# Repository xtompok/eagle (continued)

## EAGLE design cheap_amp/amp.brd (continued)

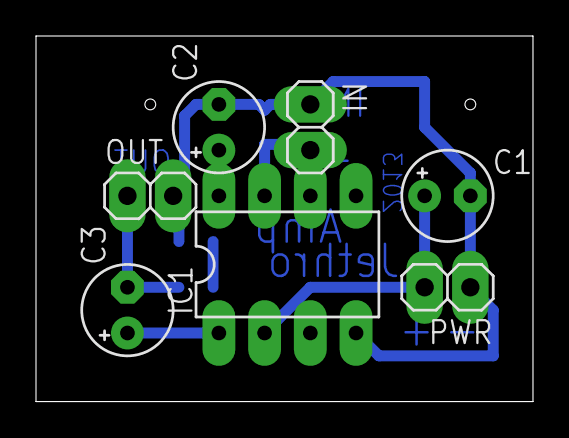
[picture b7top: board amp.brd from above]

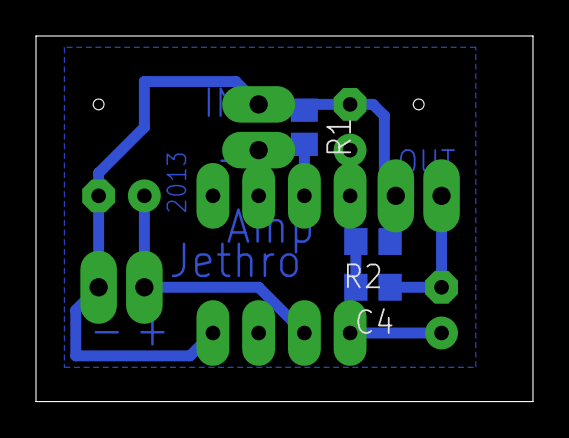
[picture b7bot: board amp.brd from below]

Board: 2 copper layers, 27.6 x 20.3 mm, 10 parts (3 on the bottom side), 7 nets.

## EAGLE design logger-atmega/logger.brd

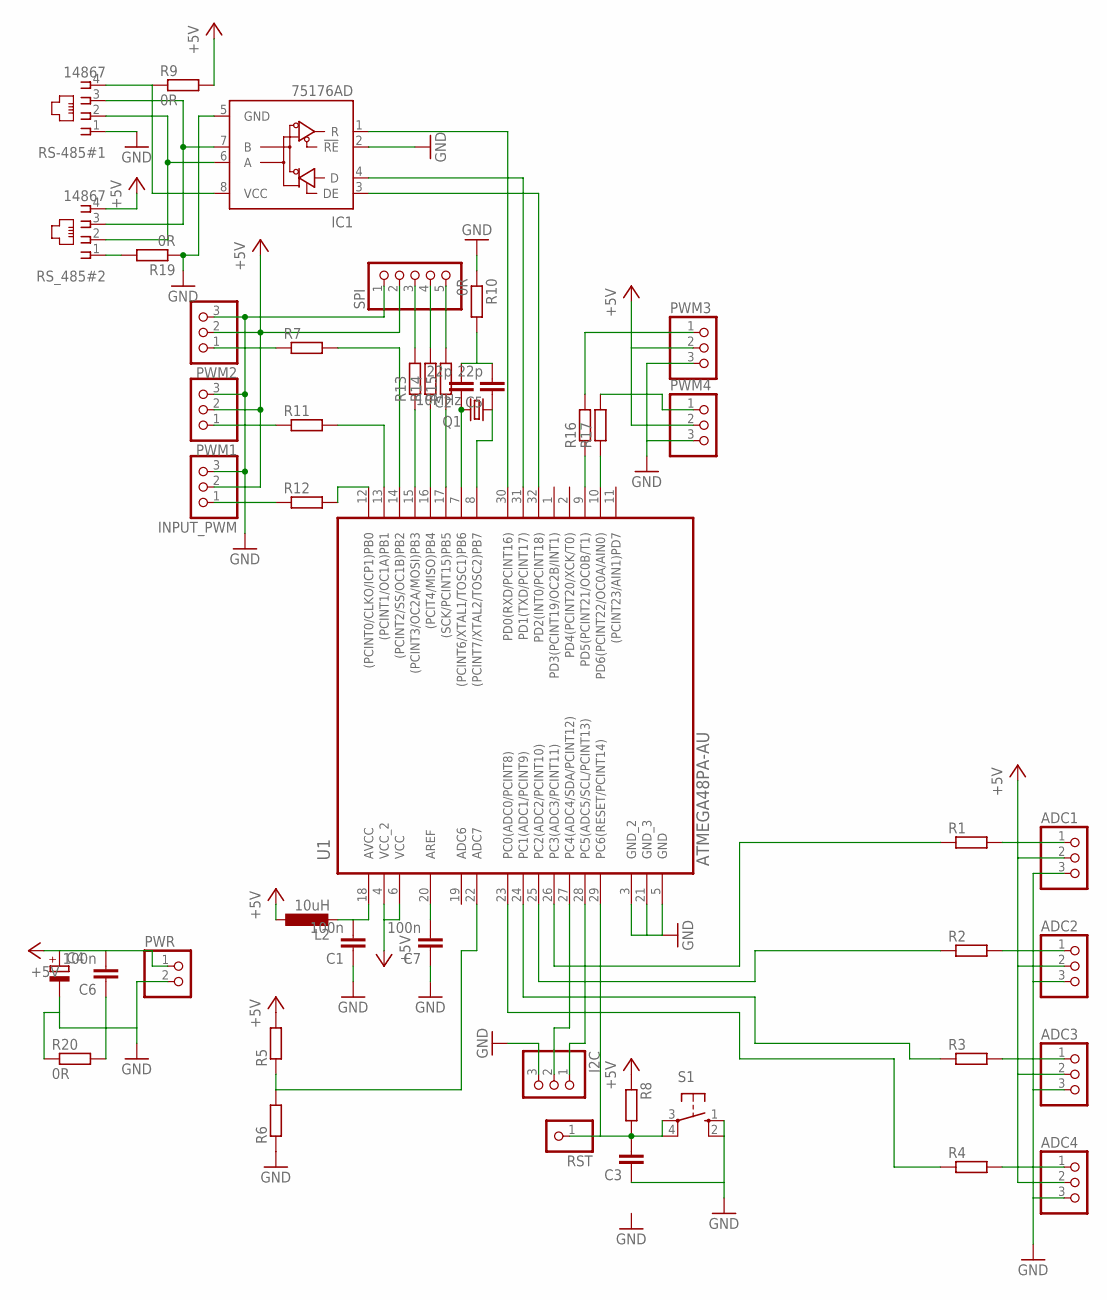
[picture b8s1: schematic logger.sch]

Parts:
ADC1, ADC2, ADC3, ADC4: PINHD-1X3; 1X03
C1, C6, C7: 100n; C0805
C2, C5: 22p; C0805
C3: C-EUC0805; C0805
C4: CPOL-EUE2,5-6E; E2,5-6E
I2C: PINHD-1X3; 1X03
IC1: 75176AD; D_R-PDSO-G8
INPUT_PWM: PINHD-1X3; 1X03
L2: 10uH; L1206
PWM1, PWM2, PWM3, PWM4: PINHD-1X3; 1X03
PWR: PINHD-1X2; 1X02
Q1: 10MHz; HC49U-V
R1, R2, R3, R4, R5, R7, R8, R11, R12, R13, R14, R15, R16, R17: R-EU_R0805; R0805
R6: R-EU_R1206; R1206
R9, R10, R19, R20: 0R; R1206
RS-485#1: 14867
RST: PINHD-1X1; 1X01
RS_485#2: 14867
S1: 10-XX; B3F-10XX
SPI: PINHD-1X5; 1X05
U1: ATMEGA48PA-AU; QFP80P900X900X120-32N

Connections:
+5V: ADC1.2, ADC2.2, ADC3.2, ADC4.2, C4.+, C6.2, INPUT_PWM.2, L2.1, PWM1.2, PWM2.2, PWM3.2, PWM4.2, PWR.1, R5.2, R8.1, R9.2, RS_485#2.4, SPI.2, U1.4 (VCC_2), U1.6 (VCC)
DE: IC1.3 (DE), U1.32 (PD2(INT0/PCINT18))
GND: ADC1.3, ADC2.3, ADC3.3, ADC4.3, C1.1, C3.1, C4.-, C6.1, C7.1, I2C.3, IC1.2 (!RE), IC1.5 (GND), INPUT_PWM.3, PWM1.3, PWM2.3, PWM3.3, PWM4.3, PWR.2, R6.1, R10.1, R19.1, R20.1, R20.2, RS-485#1.1, S1.1 (S), S1.2 (S1), SPI.1, U1.3 (GND_2), U1.5 (GND), U1.21 (GND_3)
unnamed: IC1.6 (A), RS-485#1.2, RS_485#2.2
unnamed: IC1.7 (B), RS-485#1.3, RS_485#2.3
unnamed: R5.1, R6.2, U1.22 (ADC7)
unnamed: R4.1, U1.23 (PC0(ADC0/PCINT8))
unnamed: ADC4.1, R4.2
unnamed: ADC3.1, R3.2
unnamed: ADC2.1, R2.2
unnamed: ADC1.1, R1.2
unnamed: R3.1, U1.24 (PC1(ADC1/PCINT9))
unnamed: R2.1, U1.25 (PC2(ADC2/PCINT10))
unnamed: R1.1, U1.26 (PC3(ADC3/PCINT11))
unnamed: INPUT_PWM.1, R12.1
unnamed: R15.2, SPI.5
unnamed: R14.2, SPI.4
unnamed: C3.2, R8.2, RST.1, S1.3, S1.4 (P1), U1.29 (PC6(RESET/PCINT14))
unnamed: C2.1, Q1.2, U1.7 ((PCINT6/XTAL1/TOSC1)PB6)
unnamed: R13.2, SPI.3
unnamed: C5.1, Q1.1, U1.8 ((PCINT7/XTAL2/TOSC2)PB7)
unnamed: C1.2, L2.2, U1.18 (AVCC)
unnamed: IC1.8 (VCC), R9.1, RS-485#1.4
unnamed: I2C.1, U1.28 (PC5(ADC5/SCL/PCINT13))
unnamed: I2C.2, U1.27 (PC4(ADC4/SDA/PCINT12))
unnamed: PWM1.1, R11.1
unnamed: PWM2.1, R7.1
unnamed: R13.1, U1.15 ((PCINT3/OC2A/MOSI)PB3)
unnamed: R14.1, U1.16 ((PCIT4/MISO)PB4)
unnamed: R16.1, U1.9 (PD5(PCINT21/OC0B/T1))
unnamed: R17.1, U1.10 (PD6(PCINT22/OC0A/AIN0))
unnamed: R15.1, U1.17 ((SCK/PCINT15)PB5)
unnamed: R19.2, RS_485#2.1
unnamed: R12.2, U1.12 ((PCINT0/CLKO/ICP1)PB0)
unnamed: R11.2, U1.13 ((PCINT1/OC1A)PB1)
unnamed: R7.2, U1.14 ((PCINT2/SS/OC1B)PB2)
unnamed: C7.2, U1.20 (AREF)
unnamed: C2.2, C5.2, R10.2
unnamed: PWM4.1, R17.2
unnamed: PWM3.1, R16.2
RX: IC1.1 (R), U1.30 (PD0(RXD/PCINT16))
TX: IC1.4 (D), U1.31 (PD1(TXD/PCINT17))

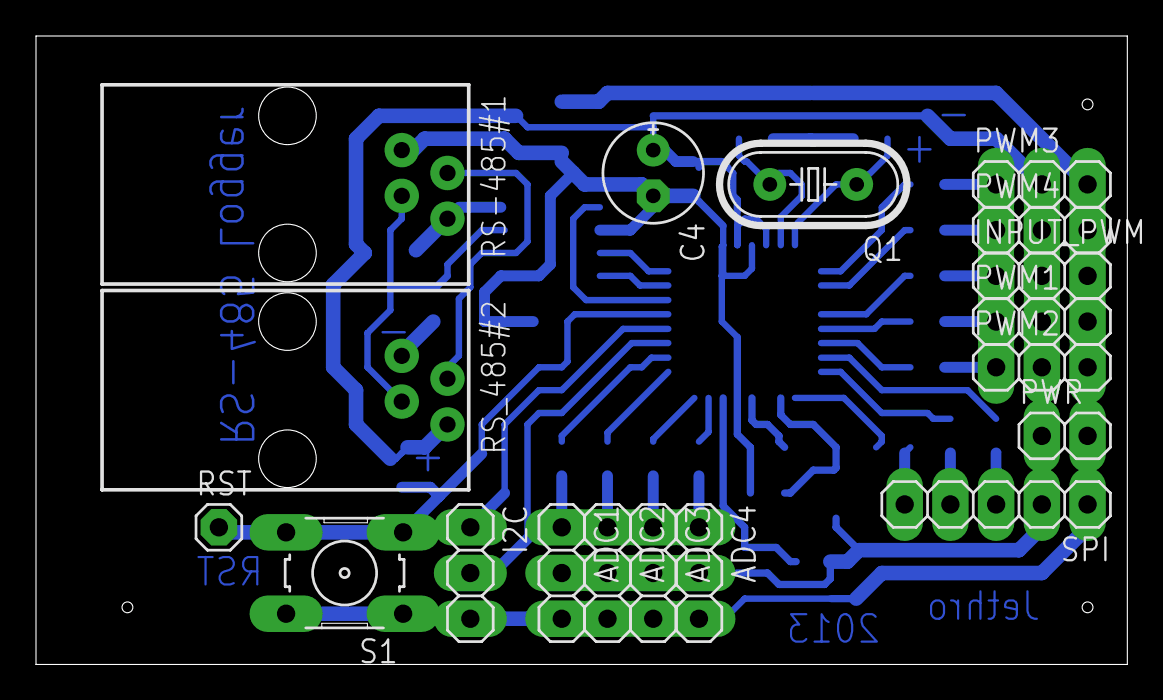
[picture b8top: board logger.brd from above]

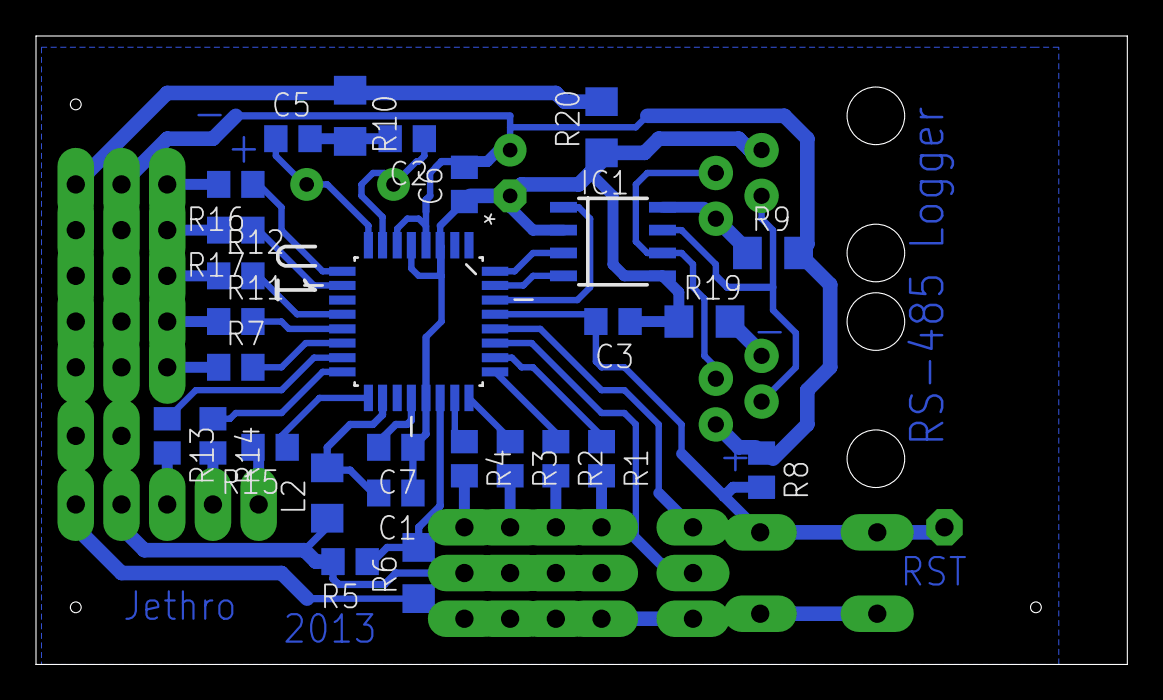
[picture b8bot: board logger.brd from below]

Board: 2 copper layers, 60.6 x 34.9 mm, 46 parts (28 on the bottom side), 42 nets.

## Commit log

2013-03-24 Breakout for magnetic encoder.
2013-03-24 removed unwanted files
2013-03-24 Added .gitignore
2013-03-24 Added description.
2013-03-24 Added logger.
2013-03-24 Added description
2013-03-24 Ignore .DS_Store
2013-03-25 Bugfixes, partially routed.
2013-03-27 Routed.
2013-03-27 Odhad ceny loggeru.
2013-03-27 Final changes.
2013-04-04 Syncing with repository
2013-04-04 copy of logger, wil be magnetic decoder.
2013-04-04 Magnetic encode with MSP430 board
2013-04-05 Commit before merge
2013-04-05 Added new logger, which will have atmega
2013-04-09 Final borad edits and ps for print
2013-04-09 Fix PS
2013-04-10 ATMega logger routed.
2013-04-24 Obrazek pro Cyrila
2013-04-26 Upravy desky i schematu, snad definitivni.
    Odebrana zenerka, budu verit vnitrni referenci
    Pridana civka na analogovou zem
    Pridan napajeci konektor
    Napajeci cesty rozsireny
    Doplneny napisy
    Vylito medi
2013-04-30 Pridan kondenzator na AREF
2013-09-10 Added cheap amplifier with TDA2822M
2013-09-22 Added 2013 to board. added .png file for print.
2013-12-20 Added converter 12V -> 5V with MC34063
2013-12-20 + Napajeci deska na robota
2013-12-20 Doplneny hodnosty soucastek
2013-12-21 Update napajeniMOB.brd
    Takto byla deska vyrobena 20.12.2013
2013-12-21 Update napajeniMOB.sch
    Takto byla deska vyrobena 20.12.2013
2013-12-26 + Added values of parts.
2014-01-04 Changed layout and some parts.
2014-07-26 Added circuit for generator from bicycle.
2014-07-26 Auto-updated eagle.epf
2014-07-26 Use N-channel MOSFET with pulldown.
2014-07-26 First version routed.
2014-07-27 Routed board.
2014-07-28 Values of parts.
2014-09-28 Added 12V to 5V switching regulator with MC34063 and MOSFET.
2014-09-28 Added level shifter for IBIS bus.
2015-02-21 Added small MSP430 board for driving NRF24L01
2015-03-27 Updated nrf transmitter.
    BUG: exchanged MISO and MOSI on MCU!
2015-03-27 Ignore Gerber files
2015-04-08 Added Stabilizer to 5V and 3V3
